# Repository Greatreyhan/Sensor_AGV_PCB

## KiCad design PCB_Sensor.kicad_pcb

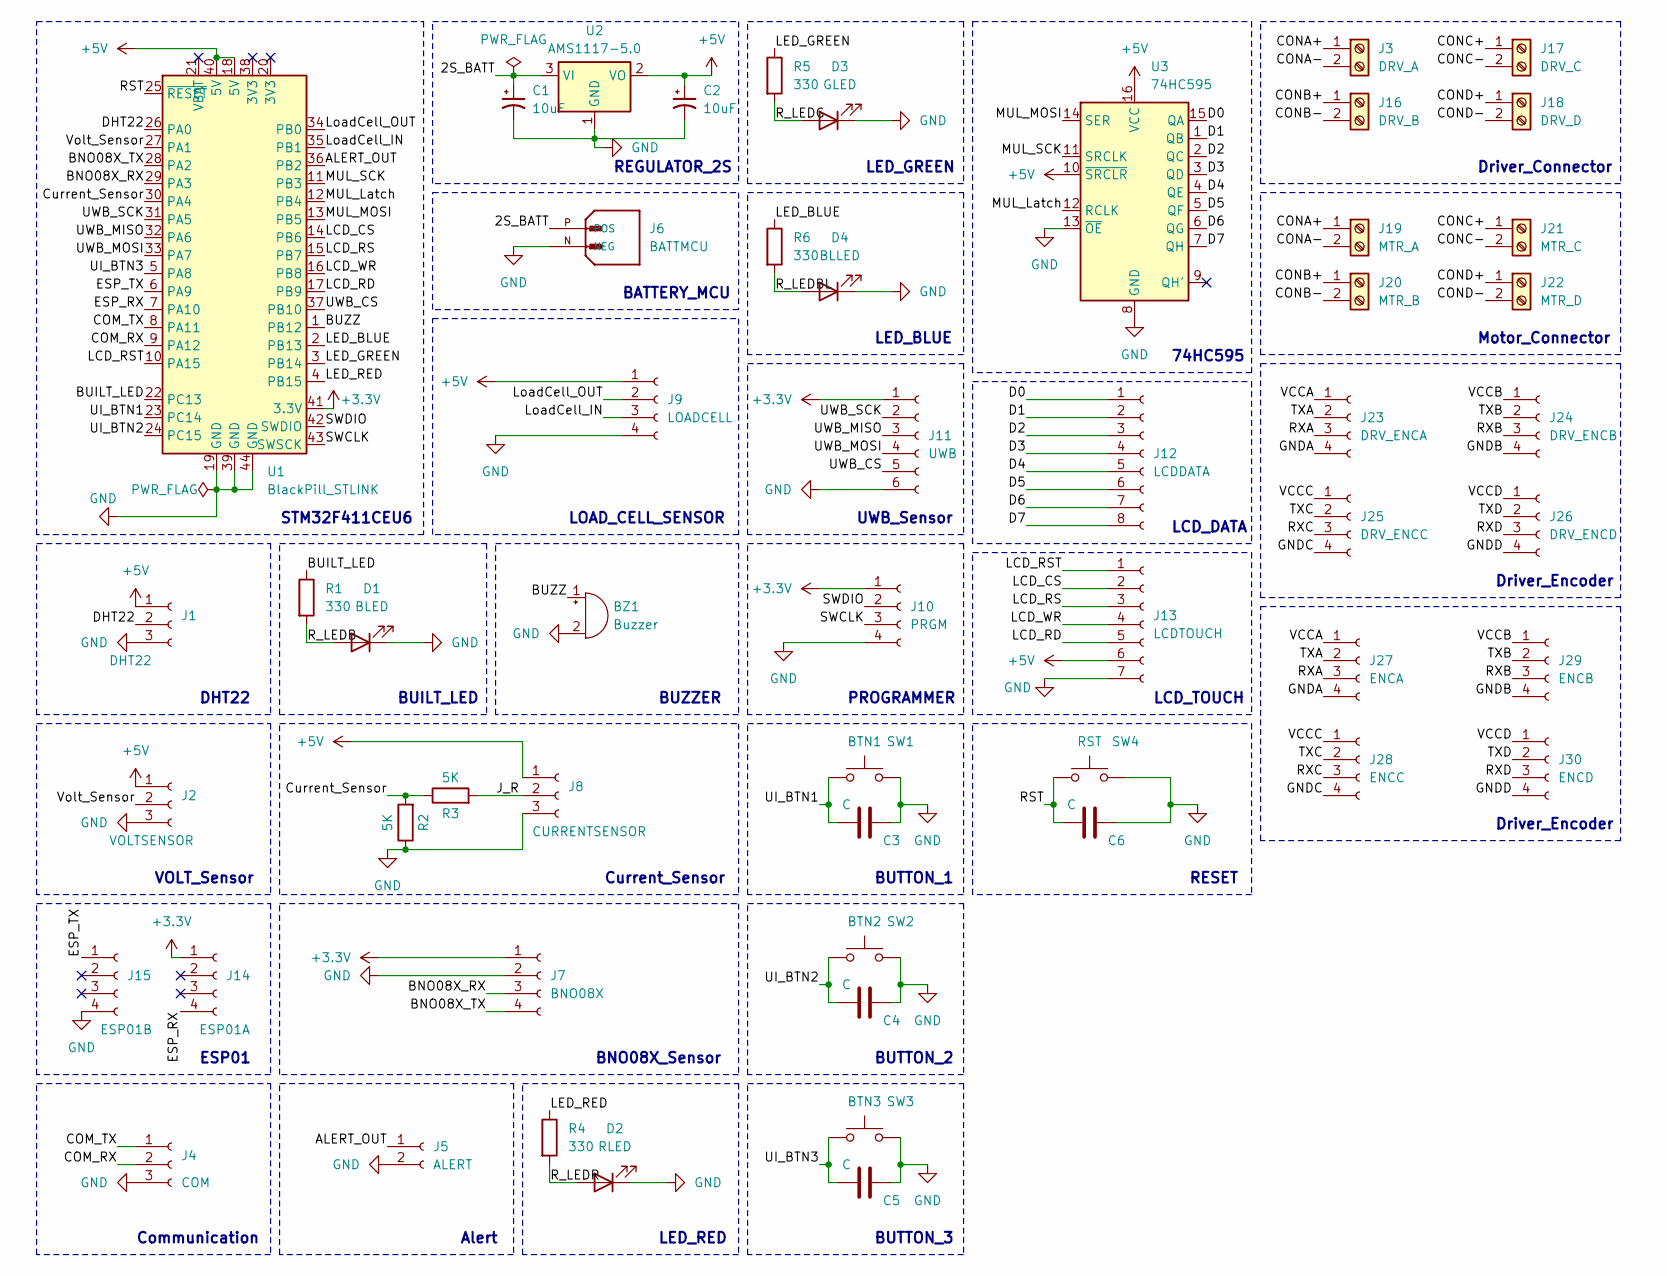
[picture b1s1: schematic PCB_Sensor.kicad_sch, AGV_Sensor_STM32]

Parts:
BZ1: Buzzer; Buzzer_15x7.5RM7.6
C1, C2: 10uF; CP_Elec_4x5.4
C3, C4, C5, C6: C; C_1206_3216Metric_Pad1.33x1.80mm_HandSolder
D1: BLED; LED_1206_3216Metric_Pad1.42x1.75mm_HandSolder
D2: RLED; LED_1206_3216Metric_Pad1.42x1.75mm_HandSolder
D3: GLED; LED_1206_3216Metric_Pad1.42x1.75mm_HandSolder
D4: BLLED; LED_1206_3216Metric_Pad1.42x1.75mm_HandSolder
J1: DHT22; PinHeader_1x03_P2.54mm_Vertical
J2: VOLTSENSOR; PinHeader_1x03_P2.54mm_Vertical
J3: DRV_A; TerminalBlock_bornier-2_P5.08mm
J4: COM; PinHeader_1x03_P2.54mm_Vertical
J5: ALERT; PinHeader_1x02_P2.54mm_Vertical
J6: BATTMCU; AMASS_XT60-M; PARTREV V00
J7: BNO08X; PinHeader_1x04_P2.54mm_Vertical
J8: CURRENTSENSOR; PinHeader_1x03_P2.54mm_Vertical
J9: LOADCELL; PinHeader_1x04_P2.54mm_Vertical
J10: PRGM; PinHeader_1x04_P2.54mm_Vertical
J11: UWB; PinHeader_1x06_P2.54mm_Vertical
J12: LCDDATA; PinHeader_1x08_P2.54mm_Vertical
J13: LCDTOUCH; PinHeader_1x07_P2.54mm_Vertical
J14: ESP01A; PinHeader_1x04_P2.54mm_Vertical
J15: ESP01B; PinHeader_1x04_P2.54mm_Vertical
J16: DRV_B; TerminalBlock_bornier-2_P5.08mm
J17: DRV_C; TerminalBlock_bornier-2_P5.08mm
J18: DRV_D; TerminalBlock_bornier-2_P5.08mm
J19: MTR_A; TerminalBlock_bornier-2_P5.08mm
J20: MTR_B; TerminalBlock_bornier-2_P5.08mm
J21: MTR_C; TerminalBlock_bornier-2_P5.08mm
J22: MTR_D; TerminalBlock_bornier-2_P5.08mm
J23: DRV_ENCA; PinHeader_1x04_P2.54mm_Vertical
J24: DRV_ENCB; PinHeader_1x04_P2.54mm_Vertical
J25: DRV_ENCC; PinHeader_1x04_P2.54mm_Vertical
J26: DRV_ENCD; PinHeader_1x04_P2.54mm_Vertical
J27: ENCA; PinHeader_1x04_P2.54mm_Vertical
J28: ENCC; PinHeader_1x04_P2.54mm_Vertical
J29: ENCB; PinHeader_1x04_P2.54mm_Vertical
J30: ENCD; PinHeader_1x04_P2.54mm_Vertical
R1, R4, R5, R6: 330; R_1206_3216Metric_Pad1.30x1.75mm_HandSolder
R2, R3: 5K; R_1206_3216Metric_Pad1.30x1.75mm_HandSolder
SW1: BTN1; SW_Push_1P1T_XKB_TS-1187A
SW2: BTN2; SW_Push_1P1T_XKB_TS-1187A
SW3: BTN3; SW_Push_1P1T_XKB_TS-1187A
SW4: RST; SW_Push_1P1T_XKB_TS-1187A
U1: BlackPill_STLINK
U2: AMS1117-5.0; SOT-223-3_TabPin2
U3: 74HC595; SOIC-16_3.9x9.9mm_P1.27mm

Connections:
+3.3V: J7.1, J10.1, J11.1, J14.1, U1.41 (3.3V)
+5V: C2.1, J1.1, J2.1, J8.1, J9.1, J13.6, U1.18 (5V), U1.40 (5V), U2.2 (VO), U3.10 (~SRCLR), U3.16 (VCC)
/2S_BATT: C1.1, J6.P (POS), U2.3 (VI)
/ALERT_OUT: J5.1, U1.36 (PB2)
/BNO08X_RX: J7.3, U1.29 (PA3)
/BNO08X_TX: J7.4, U1.28 (PA2)
/BUILT_LED: R1.1, U1.22 (PC13)
/BUZZ: BZ1.1 (-), U1.1 (PB12)
/COM_RX: J4.2, U1.9 (PA12)
/COM_TX: J4.1, U1.8 (PA11)
/CONA+: J3.1, J19.1
/CONA-: J3.2, J19.2
/CONB+: J16.1, J20.1
/CONB-: J16.2, J20.2
/CONC+: J17.1, J21.1
/CONC-: J17.2, J21.2
/COND+: J18.1, J22.1
/COND-: J18.2, J22.2
/Current_Sensor: R2.2, R3.1, U1.30 (PA4)
/D0: J12.1, U3.15 (QA)
/D1: J12.2, U3.1 (QB)
/D2: J12.3, U3.2 (QC)
/D3: J12.4, U3.3 (QD)
/D4: J12.5, U3.4 (QE)
/D5: J12.6, U3.5 (QF)
/D6: J12.7, U3.6 (QG)
/D7: J12.8, U3.7 (QH)
/DHT22: J1.2, U1.26 (PA0)
/ESP_RX: J14.4, U1.7 (PA10)
/ESP_TX: J15.1, U1.6 (PA9)
/GNDA: J23.4, J27.4
/GNDB: J24.4, J29.4
/GNDC: J25.4, J28.4
/GNDD: J26.4, J30.4
/J_R: J8.2, R3.2
/LCD_CS: J13.2, U1.14 (PB6)
/LCD_RD: J13.5, U1.17 (PB9)
/LCD_RS: J13.3, U1.15 (PB7)
/LCD_RST: J13.1, U1.10 (PA15)
/LCD_WR: J13.4, U1.16 (PB8)
/LED_BLUE: R6.1, U1.2 (PB13)
/LED_GREEN: R5.1, U1.3 (PB14)
/LED_RED: R4.1, U1.4 (PB15)
/LoadCell_IN: J9.3, U1.35 (PB1)
/LoadCell_OUT: J9.2, U1.34 (PB0)
/MUL_Latch: U1.12 (PB4), U3.12 (RCLK)
/MUL_MOSI: U1.13 (PB5), U3.14 (SER)
/MUL_SCK: U1.11 (PB3), U3.11 (SRCLK)
/RST: C6.1, SW4.1, U1.25 (~RESET)
/RXA: J23.3, J27.3
/RXB: J24.3, J29.3
/RXC: J25.3, J28.3
/RXD: J26.3, J30.3
/R_LEDB: D1.2 (A), R1.2
/R_LEDBL: D4.2 (A), R6.2
/R_LEDG: D3.2 (A), R5.2
/R_LEDR: D2.2 (A), R4.2
/SWCLK: J10.3, U1.43 (SWSCK)
/SWDIO: J10.2, U1.42 (SWDIO)
/TXA: J23.2, J27.2
/TXB: J24.2, J29.2
/TXC: J25.2, J28.2
/TXD: J26.2, J30.2
/UI_BTN1: C3.1, SW1.1, U1.23 (PC14)
/UI_BTN2: C4.1, SW2.1, U1.24 (PC15)
/UI_BTN3: C5.1, SW3.1, U1.5 (PA8)
/UWB_CS: J11.5, U1.37 (PB10)
/UWB_MISO: J11.3, U1.32 (PA6)
/UWB_MOSI: J11.4, U1.33 (PA7)
/UWB_SCK: J11.2, U1.31 (PA5)
/VCCA: J23.1, J27.1
/VCCB: J24.1, J29.1
/VCCC: J25.1, J28.1
/VCCD: J26.1, J30.1
/Volt_Sensor: J2.2, U1.27 (PA1)
GND: BZ1.2 (+), C1.2, C2.2, C3.2, C4.2, C5.2, C6.2, D1.1 (K), D2.1 (K), D3.1 (K), D4.1 (K), J1.3, J2.3, J4.3, J5.2, J6.N (NEG), J7.2, J8.3, J9.4, J10.4, J11.6, J13.7, J15.4, R2.1, SW1.2, SW2.2, SW3.2, SW4.2, U1.19 (GND), U1.39 (GND), U1.44 (GND), U2.1 (GND), U3.8 (GND), U3.13 (~OE)

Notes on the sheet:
PROGRAMMER
UWB_Sensor
LOAD_CELL_SENSOR
LED_GREEN
LCD_DATA
BATTERY_MCU
Driver_Encoder
ESP01
LED_RED
RESET
Motor_Connector
STM32F411CEU6
VOLT_Sensor
BUTTON_1
74HC595
Alert
Current_Sensor
DHT22
BUILT_LED
BUZZER
REGULATOR_2S
LED_BLUE
BUTTON_2
LCD_TOUCH
BNO08X_Sensor
Driver_Connector
Communication
BUTTON_3

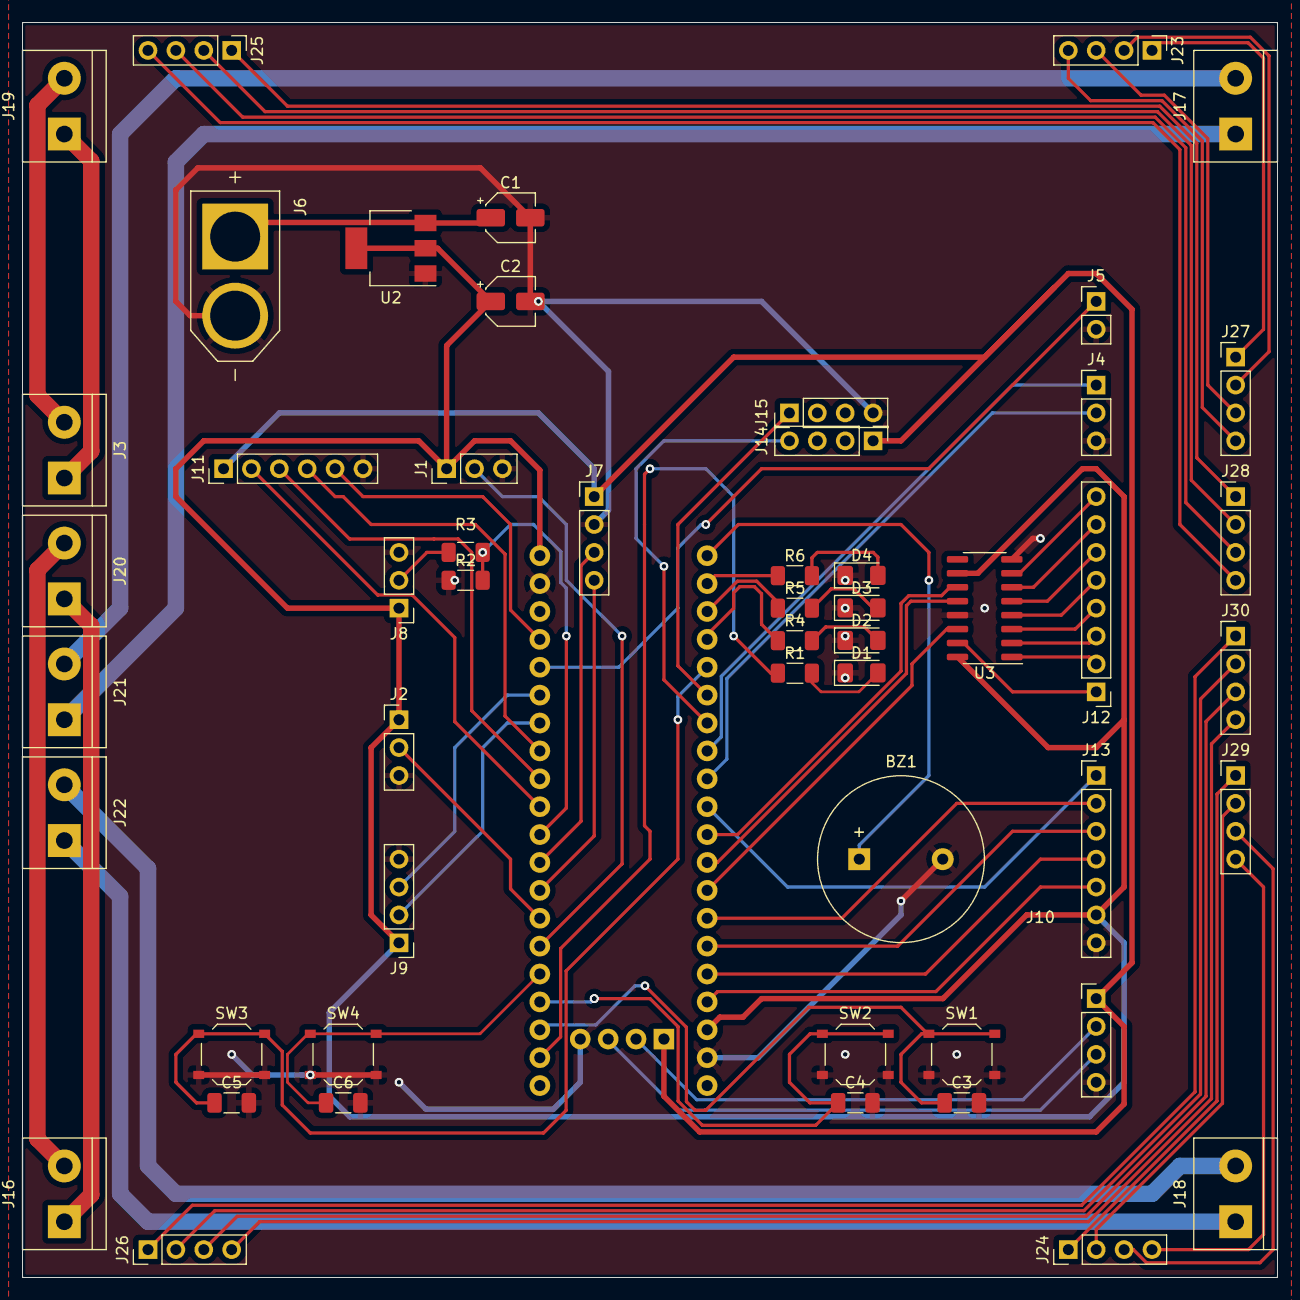
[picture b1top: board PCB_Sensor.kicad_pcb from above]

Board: 2 copper layers, 114.3 x 114.3 mm, 54 parts (1 on the bottom side), 76 nets.

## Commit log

2024-01-15 ready to print
2024-01-15 generate gerber file
